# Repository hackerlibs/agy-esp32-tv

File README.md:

# AGY TV -- 把 Antigravity (AGY) 会话详情与进度显示在小电视上

把一块 ESP32-C3「小电视」（240x240 SPI 彩屏）改造成 **Antigravity (AGY)** 桌面状态显示器：屏幕实时显示当前 AGY 会话的状态（思考中 / 运行工具 / 等待输入 / 错误 / 完成 / 待机）、`update_steps` 步骤进度条与百分比、当前步骤说明、当前工具与命令/文件详情、模型名称、上下文与输出 Token 用量、子代理 / 后台任务数、用时和时钟。

主机侧通过 **AGY 生命周期 hooks**（`hooks.json`）抓取实时事件，并结合 `transcript.jsonl` 增量解析补齐真实模型名、Token 统计、思考摘要和最终回复；即使未重启 AGY 加载 hooks，桥接进程也可自动追踪最新活跃的 `transcript.jsonl`。

```
AGY hooks (6 种事件) ──► host/agy_tv.py hook ──► bridge 常驻进程 (+ transcript.jsonl 解析)
   (安全透传、永不阻塞)       (AF_UNIX DGRAM)         (状态机 + 心跳 + 串口自动重连)
                                                            │
                                                            ▼ USB Serial/JTAG (ZTV1 协议)
                                                      ESP32-C3 固件 ──► 240x240 彩屏
```

离屏渲染的全部 26 个界面见 `tools/uitest/run.sh` 生成的拼图（含中文界面），默认输出到 `/tmp/agy-tv-ui/sheet.png`。

> **想从零 DIY 这台设备 / 学习用万用表、示波器、USB-TTL、逻辑分析仪调试 ESP32 彩屏？**
> 详见 **[docs/ 硬件与调试文档中心](./docs/README.md)**（含 ESP32-C3 原理、屏幕选型与背光电路、四类仪器实战排障与 6 步点亮路线）。

## 显示内容一览

- **顶部状态栏**：`AGY TV` / `IDLE` / `THINKING` / `RUNNING` / `WAIT INPUT`（如 `ask_question`）/ `ERROR` / `DONE` / `NO HOST` / `NO USB` + 右上角链路状态 LED。
- **核心详情区**：
  - 思考中显示当前 Prompt 与调用轮次（`INV`）；
  - 运行工具显示工具名（`run_command` / `edit_file` / `subagent` / `grep` / `ask_question` 等）和命令/路径/参数摘要，超长文本自动水平往返滚动；
- **进度与活动区**：
  - 当 AGY 调用 `update_steps` 时，显示 `STEPS` 进度条、`完成/总数 百分比%` 与当前 `in_progress` 步骤标题；
  - 无步骤清单时自动切换为 `ACTIVITY`（当前目标/思考摘要）或 `PROGRESS` 动态活动条 + `STEP` 步数；
- **AGY 遥测条**：左侧显示解析出的实际模型名（如 `gemini-4-neon-high`），右侧显示上下文 Token（`CTX 89.4K`）；
- **底部统计与页脚**：左侧大字本轮用时（`ELAPSED`），右侧显示工具调用数（`TOOLS`）、子代理/后台任务数（`SUB` / `BG`）或输出 Token（`OUT`）、失败次数（`FAIL`）；页脚显示时钟与当前项目名（支持中文）。

## 硬件结论（来自对原厂固件的逆向）

原固件是 Arduino + TFT_eSPI 的「小电视」固件（开源项目 SmallDesktopDisplay 的定制版，源码见卖家提供的 `时钟/C3版本`）。屏幕引脚最初通过反汇编其 flash 备份得出，后与源码逐项核对一致：

| 项目 | 值 | 来源 |
|---|---|---|
| 主控 | ESP32-C3 (QFN32) rev 0.4，4MB flash | esptool flash-id |
| 屏幕 | 240x240、RGB565、IPS（需 INVON）、原生方向（MADCTL=0） | 原固件初始化命令表（rodata 0x3C28EE80） |
| SPI | mode 3，引脚 SCLK=3、MOSI=5（均为 FSPI 原生脚） | `SPIClass::begin(3, 5, 5, -1)` 反汇编 |
| DC / RST | GPIO2 / GPIO6（复位脉冲 20ms 低 + 150ms） | `pinMode`/`digitalWrite` 调用点反汇编 |
| CS | 未接（拉低） | `spi.begin(..., ss=-1)` |
| **背光** | **GPIO1，PWM 调光（LEDC）** | 源码 `User_Setup.h: #define TFT_BL 1`、`.ino: #define LCD_BL_PIN 1` + `analogWrite()` |

flash 分区（原厂）：nvs @0x9000、otadata、app0 @0x10000 (3MB)、spiffs @0x310000（相册）、coredump。
本固件只写 0x0..0x4B000（bootloader/分区表/app），**不碰 NVS 和相册**，随时可完整还原。

> **踩坑记录：背光**。排查黑屏先确认背光（`ZTV1 C bl`），再查显示数据。

## 仓库结构

```
main/            固件 (ESP-IDF v5.5, C)
  main.c           入口：面板初始化 → 链接 → 渲染任务
  panel.c          SPI 面板驱动（含 32KB DMA 分块）
  gfx.c            帧缓冲绘图层：脏行跟踪、混合文本（ASCII 5x8 + 中文 12px，无损 CJK 换行）
  zmodel.c         共享状态模型（含 AGY 模型/Token/步骤/子任务字段；演示模式样本）
  ui.c             AGY TV 九种状态界面；部件级局部重绘
  zlink.c          串口帧协议解析（向后兼容 ZTV1，容错忽略未知键与畸形行）
  port_esp.c       平台接缝（时钟/USB/互斥），使 ui/gfx/zmodel 可在桌面编译
  fonts/           生成的字库 + 三个开源字体的许可证
host/
  agy_tv.py        AGY bridge 常驻进程 + AGY hook 入口 + transcript.jsonl 追踪
  install_hooks.py 把 AGY hooks 写入 ~/.gemini/config/hooks.json（全局）或 .agents/hooks.json
  zcode_tv.py      兼容入口（转发到 agy_tv.py）
.agents/
  hooks.json       本仓库自带的便携工作区 AGY hooks 配置
tools/
  gen_fonts.py       字库生成（开发期，固件只 include 产物）
  uitest/            离屏渲染测试：无硬件验证全部界面 + 面板一致性校验（支持纯 Python 输出 PNG）
  build.sh           构建/烧录包装（支持 macOS /dev/cu.usbmodem* 与 Linux /dev/ttyACM*）
  flash_rfc2217.py   远程 RFC2217 专用刷机脚本（解决 ESP32-C3 USB 重枚举与 RFC2217 超时卡慢）
  monitor.sh         不会复位板子的串口监视器（支持本地串口与 rfc2217://）
  restore_original.sh 一键还原原厂固件（备份在 backup/，已校验）
backup/
  esp32c3_original_4MB.bin  原厂固件完整备份（含 WiFi 配置；勿提交，已在 .gitignore）
```

## 构建与烧录

依赖：ESP-IDF v5.5（如装在 `~/esp/esp-idf`，或通过 `IDF_PATH` 指定）。

```bash
tools/build.sh --flash        # 构建并烧录（自动找 /dev/cu.usbmodem* 或 /dev/ttyACM*）
tools/build.sh --monitor      # 烧录后打开串口监视（不会复位板子）
idf.py -p <port> menuconfig   # 引脚/时钟/旋转等全部可配 (AGY TV 菜单)
```

> **提示**：新版主机脚本 `host/agy_tv.py` 保持与旧版 v1 固件的 `ZTV1` 串口协议兼容；未重烧固件前也可直接显示状态、工具与步骤进度，重烧 v2.0.0 固件后即可解锁完整 AGY TV 界面（模型名、Token、步骤百分比、`SUB`/`BG` 计数等）。

无主机验证：烧录后屏幕自行显示 BOOT → NO HOST；也可以发 `ZTV1 C demo=1` 循环播放 AGY 演示数据（menuconfig 里 `ZTV_UI_DEMO_ON_BOOT` 可设为开机即演示）。

## 主机侧安装与启动

```bash
# 1. 安装 AGY 全局 hooks（~/.gemini/config/hooks.json，所有项目自动生效）
python3 host/install_hooks.py

# 或仅安装在某个工作区的 .agents/hooks.json：
# python3 host/install_hooks.py --workspace

# 2. 启动串口桥接（本地 USB 自动发现，也支持 rfc2217://；无需设备时可加 --dry-run 预览帧）
python3 host/agy_tv.py bridge --daemon
# 远程 RFC2217 桥接示例（也可通过环境变量 AGY_TV_PORT 指定）：
# python3 host/agy_tv.py bridge --port 'rfc2217://127.0.0.1:4000?ign_set_control' --daemon

# 3. 查看桥接状态、日志，或在线调节背光亮度（无需停止桥接）
python3 host/agy_tv.py status
tail -f /tmp/agy-tv.log
python3 host/agy_tv.py bl 80         # 设置背光亮度 0..100%（实时生效）
python3 host/agy_tv.py bl            # 查询当前亮度、原始 PWM 占空比与极性
python3 host/agy_tv.py bl --raw 50   # 直接设置 8-bit LEDC 原始占空比 (0..256)
python3 host/agy_tv.py bl --inv 1    # 切换背光极性（1=低电平亮/默认，0=高电平亮）
```

- Hooks 严格遵循 AGY `hooks.json` 契约：`PreToolUse` 返回 `{"decision": "allow"}`（交给默认权限策略，**绝不**绕过授权确认），`Stop` 返回 `{"decision": "stop"}`，其余返回 `{}`，永远 exit 0，桥接未开或板子未插都不会阻塞 AGY。
- 卸载 hooks：`python3 host/install_hooks.py --remove`（或加 `--workspace`）。
- 即使尚未重启 AGY 会话，bridge 也会自动扫描 `~/.gemini/{antigravity-cli,antigravity,antigravity-ide}/brain/*/.system_generated/logs/transcript.jsonl` 追踪最近活跃会话（可用 `--no-watch` 关闭）。

## 远程刷机与远程驱动教程（RFC2217 + SSH 反向代理）

如果你的 **AGY 运行在远程 Linux 服务器**，而 **ESP32-C3 插在本地 Mac/电脑上**，可以通过 `esp_rfc2217_server` + SSH 反向端口转发，在远程服务器上直接编译、刷机并实时驱动小电视。

### 第 1 步：在本地电脑（插着 ESP32 的机器）启动 RFC2217 服务端

> **关键踩坑（ESP32-C3 内置 USB-Serial/JTAG 必看）**：
> `esp_rfc2217_server.py` 默认会拦截客户端的 DTR/RTS 并在服务端执行 `UnixTightReset`（传统 CP2102/CH340 串口芯片用的时序），会导致 ESP32-C3 每次复位都进入 `boot:0xd (SPI_FAST_FLASH_BOOT)` 而无法进入下载模式。
> **解法**：写入 `esptool.cfg` 指定 ESP32-C3 USB-Serial/JTAG 的下载模式复位时序，并通过 `ESPTOOL_CFGFILE` 加载：

```bash
# 1. 创建 ESP32-C3 USB-Serial/JTAG 复位配置
cat > /tmp/esptool_c3.cfg <<'EOF'
[esptool]
custom_reset_sequence = R0|D0|W0.1|D1|R0|W0.1|R1|D0|R1|W0.1|D0|R0
EOF

# 2. 启动 RFC2217 服务端（启动输出必须看到 Loaded custom configuration from /tmp/esptool_c3.cfg）
ESPTOOL_CFGFILE=/tmp/esptool_c3.cfg \
  ~/.espressif/python_env/idf5.5_py3.13_env/bin/esp_rfc2217_server.py \
  -v -p 4000 /dev/cu.usbmodem14201
```

### 第 2 步：把本地 4000 端口反向代理到远程 Linux 服务器

在本地再开一个终端（或合并进你的 SSH 登录命令）：

```bash
ssh -N -R 4000:127.0.0.1:4000 <user>@<remote-server>
```

在远程服务器上可用 `ss -tlnp | grep 4000` 确认 `127.0.0.1:4000` 已监听。

### 第 3 步：在远程服务器编译并远程刷机

```bash
# 0. 如果 bridge 正在运行，先停掉（esp_rfc2217_server 同一时间只接受一个 TCP 连接）
kill $(cat /tmp/agy-tv.bridge.pid) 2>/dev/null || true

# 1. 编译固件（仅需安装 esp32c3 目标的 ESP-IDF v5.5）
tools/build.sh

# 2. 使用远程刷机脚本写入（分段写入 0x0 / 0x8000 / 0x10000，不碰 NVS 和原厂相册）
python3 tools/flash_rfc2217.py

# 之后如果只改了应用代码（没改分区表/bootloader），可只刷主程序更快：
python3 tools/flash_rfc2217.py --app-only
```

> **为什么要用 `tools/flash_rfc2217.py` 而不是裸跑 `esptool.py`？**（实测踩坑总结）
> 1. **参数拼写**：pyserial RFC2217 的选项是单数 `ign_set_control`（不是 `ign_set_controls`）。
> 2. **打开端口的复位竞态**：`esp_rfc2217_server` 在 TCP 连上（`DTR_ON`）时就会触发 `custom_reset_sequence`（耗时约 0.3s）；若客户端再跑 `default_reset`，发出的 `DTR_OFF`/`RTS_OFF` 会把芯片踢出下载模式。脚本使用 `--before no_reset`，连上后等待 0.6s 再发 `SYNC`（并将 `SYNC_TIMEOUT` 调到 0.5s 适应隧道 RTT）。
> 3. **macOS USB 重枚举（`Errno 6: Device not configured`）**：在 ESP32-C3 USB-Serial/JTAG 上上传并切换 RAM stub 时容易触发 macOS 重新枚举 `/dev/cu.usbmodem*`，导致服务端 fd 失效。脚本使用 `--no-stub --compress` 留在芯片 mask ROM 中直接解压写入，稳定不掉线。
> 4. **pyserial RFC2217 卡慢 10 倍**：`esptool` 每写入一个块都会保存/恢复 `port.timeout`，而 pyserial 的 `rfc2217.Serial.timeout` 每次被赋值都会重新发起 4 项 Telnet 串口参数协商（把刷机拖慢到 ~4 kbit/s）。脚本在 `open()` 之后覆写 `timeout` setter 跳过无意义的远端协商，实测提速约 9 倍（459KB 压缩为 224KB，约 105 秒刷完，有效速率 ~35 kbit/s）。

### 第 4 步：在远程服务器启动 AGY 实时桥接

刷完固件后，直接把 `agy_tv.py` 连到反向代理端口，即可让本地桌面的小电视实时显示远程服务器上的 AGY 详情进度：

```bash
# 安装远程服务器全局 AGY hooks（~/.gemini/config/hooks.json）
python3 host/install_hooks.py

# 启动远程 RFC2217 桥接（会自动跳过 rfc2217 不支持的 write_timeout，并在连上后退出下载模式正常启动固件）
nohup python3 host/agy_tv.py bridge \
  --port 'rfc2217://127.0.0.1:4000?ign_set_control' \
  --daemon >/dev/null 2>&1 </dev/null

# 验证连接与实时日志
python3 host/agy_tv.py status
tail -f /tmp/agy-tv.log
```

## 真机实测性能（AGY TV v2.0.0）

| 项目 | 实测值 |
|---|---|
| 固件体积 | `449 KB`（`0x70400`，3MB app 分区空闲 85%） |
| 空闲堆内存 | `187.9 KB` |
| 静止帧渲染耗时 | `28 us`（0 行 SPI 流量） |
| 动画帧渲染耗时 | `~10.3 ms` |
| 最慢全屏刷新 | `41.0 ms`（20fps 预算 50ms） |
| 背光状态 | GPIO1 PWM `duty=255` |

恢复原厂固件（天气时钟 + 相册，含全部设置）：

```bash
tools/restore_original.sh
```

## 串口协议（115200，行式 ASCII，兼容 ZTV1）

主机 → 设备（每帧是完整快照，未知键自动忽略）：

```
ZTV1 S st=<idle|think|tool|perm|err|done> tool="run_command" n=7 f=1 el=42 todo=2/4
      cur="当前步骤" msg="命令或提示文本" proj="esp32_tv" sid="a3653af3"
      clk="14:02:11" date="2026-11-27 FRI"
      model="gemini-4-neon-high" inv=4 step=18 ctx=89400 out=3720 sub=1 bg=1
ZTV1 C ping | stats | get | bl[=<0..100>] | bl_raw=<0..256> | bl_inv=<0|1> | demo=<0|1> | rot=<0..3> | reboot
```

设备 → 主机：`ZTV1 R hello|pong|state ...|stats ...|bl ...`。`msg/cur/proj` 为 UTF-8，设备用 GB2312 字库渲染（7445 字，~190KB 在 flash，不占 RAM）；字库外的字符（emoji 等）跳过。

## 疑难排解

- **屏幕全黑但串口正常（`ZTV1 C stats` 帧数在涨）**：检查背光 `ZTV1 C bl`。
- **板子看起来「死」了 / 启动不起来**：ESP32-C3 的 USB-Serial/JTAG 用 DTR/RTS 控制 EN/IO0。不要用会拉低 IO0 的普通串口工具；重新插拔 USB 或使用 `tools/monitor.sh` 即可。
- **端口被占用**：桥接运行时独占端口。先 `kill $(cat /tmp/agy-tv.bridge.pid)`。
- **屏幕方向不对**：`python3 host/agy_tv.py send "ZTV1 C rot=0"`（支持 `0..3`）。

## 测试

- `tools/uitest/run.sh`：在桌面用 `clang` 或 `gcc`（开启 `-Wall -Wextra -Werror` + ASan/UBSan）编译真实的 `ui.c`/`gfx.c`/`zmodel.c`，渲染 26 个 AGY 屏幕场景，并逐帧校验模拟面板与帧缓冲逐字节一致（598 帧 0 差异）。无需 Pillow 也能通过纯 Python 生成 `sheet.png` 与单张 PNG。

## 字体许可

`main/fonts/` 内含三份许可证：Press Start 2P（OFL-1.1）、Spleen（BSD-2-Clause）、Cubic 11（OFL-1.1，基于 M+ BITMAP FONTS）。均允许固件捆绑；生成器 `tools/gen_fonts.py`。

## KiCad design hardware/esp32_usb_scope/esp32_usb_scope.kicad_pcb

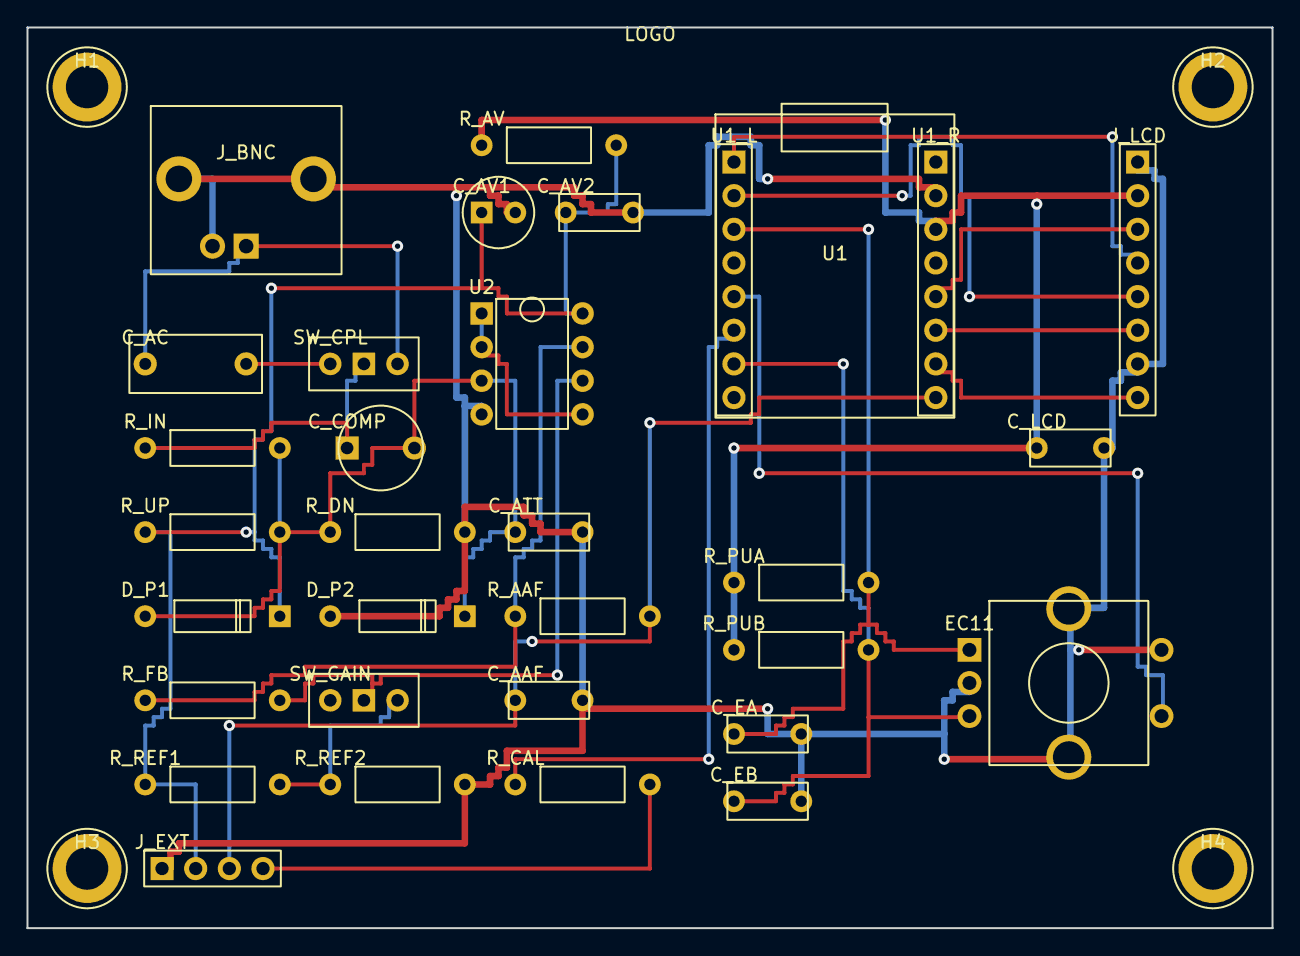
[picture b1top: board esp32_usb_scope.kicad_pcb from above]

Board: 2 copper layers, 94.0 x 68.0 mm, 37 parts (0 on the bottom side), 22 nets.

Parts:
C_AAF: 1nF; C_Disc_D5.0mm_P5.08mm
C_AC: 0.1u 250V; C_Film_L10mm_P7.62mm
C_ATT: 180pF; C_Disc_D5.0mm_P5.08mm
C_AV1: 10uF; CP_Radial_D5.0mm_P2.54mm
C_AV2: 100n; C_Disc_D5.0mm_P5.08mm
C_COMP: 5-30pF; C_Trim_6mm_P5.08mm
C_EA: 10nF; C_Disc_D5.0mm_P5.08mm
C_EB: 10nF; C_Disc_D5.0mm_P5.08mm
C_LCD: 100nF; C_Disc_D5.0mm_P5.08mm
D_P1, D_P2: 1N4148; D_DO-35_P10.16mm
EC11: TIME/TRIG; RotaryEncoder_Alps_EC11E-Switch_Vertical_H20mm
H1, H2, H3, H4: M3; MountingHole_3.2mm_M3
J_BNC: BNC-JACK; Connector_BNC_RA_P10.16mm
J_EXT: AFE-OUT-4P; PinHeader_1x04_P2.54mm
J_LCD: ST7789-8P; PinHeader_1x08_P2.54mm
LOGO: ESP32-USB-SCOPE; Silkscreen
R_AAF: 1k; R_Axial_DIN0207_L6.3mm_P10.16mm
R_AV: 10R; R_Axial_DIN0207_L6.3mm_P10.16mm
R_CAL: 1k; R_Axial_DIN0207_L6.3mm_P10.16mm
R_DN: 100k; R_Axial_DIN0207_L6.3mm_P10.16mm
R_FB: 39k; R_Axial_DIN0207_L6.3mm_P10.16mm
R_IN: 910k; R_Axial_DIN0207_L6.3mm_P10.16mm
R_PUA: 10k; R_Axial_DIN0207_L6.3mm_P10.16mm
R_PUB: 10k; R_Axial_DIN0207_L6.3mm_P10.16mm
R_REF1: 22k; R_Axial_DIN0207_L6.3mm_P10.16mm
R_REF2: 20k; R_Axial_DIN0207_L6.3mm_P10.16mm
R_UP: 100k; R_Axial_DIN0207_L6.3mm_P10.16mm
SW_CPL: AC/DC; SW_Slide_SPDT_P2.54mm
SW_GAIN: X1/X5; SW_Slide_SPDT_P2.54mm
U1: ESP32-C3 SuperMini; Module_ESP32-C3_SuperMini
U1_L: ESP32-C3-SM-L; PinHeader_1x08_P2.54mm
U1_R: ESP32-C3-SM-R; PinHeader_1x08_P2.54mm
U2: MCP6002; DIP-8_W7.62mm_Socket

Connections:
3V3: C_LCD.1, J_LCD.2, R_AV.1, R_PUA.1, R_PUB.1, U1_R.3
AFE_N1: C_ATT.1, C_COMP.2, D_P1.1, D_P2.2, R_DN.1, R_IN.2, R_UP.2, U2.3
AFE_OUT: C_AAF.1, J_EXT.3, R_AAF.2, U1_R.8
AMP_OUT: R_AAF.1, R_FB.1, U2.7
AVDD: C_AV1.1, C_AV2.1, D_P1.2, J_EXT.2, R_AV.2, R_REF1.1, R_UP.1, U2.8
BNC_AC: C_AC.2, SW_CPL.1
BNC_IN: C_AC.1, J_BNC.SIG, SW_CPL.3
CAL_1KHZ: J_EXT.4, R_CAL.2
CAL_PWM: R_CAL.1, U1_L.6
CPL_OUT: C_COMP.1, R_IN.1, SW_CPL.2
EC11_A: C_EA.1, EC11.A, R_PUA.2, U1_L.3
EC11_B: C_EB.1, EC11.B, R_PUB.2, U1_L.7
EC11_SW: EC11.S1, U1_L.5
GND: C_AAF.2, C_ATT.2, C_AV1.2, C_AV2.2, C_EA.2, C_EB.2, C_LCD.2, D_P2.1, EC11.C, EC11.MP1, EC11.MP2, EC11.S2, J_BNC.GND, J_BNC.SH1, J_BNC.SH2, J_EXT.1, J_LCD.1, J_LCD.7, R_DN.2, R_REF2.2, U1_R.2, U2.4
G_INV: R_FB.2, SW_GAIN.2, U2.6
LCD_BL: J_LCD.8, U1_R.7
LCD_DC: J_LCD.6, U1_R.6
LCD_MOSI: J_LCD.4, U1_L.1
LCD_RST: J_LCD.5, U1_L.2
LCD_SCLK: J_LCD.3, U1_R.5
VREF_DIV: R_REF1.2, R_REF2.1, SW_GAIN.3
V_BUF: U2.1, U2.2, U2.5

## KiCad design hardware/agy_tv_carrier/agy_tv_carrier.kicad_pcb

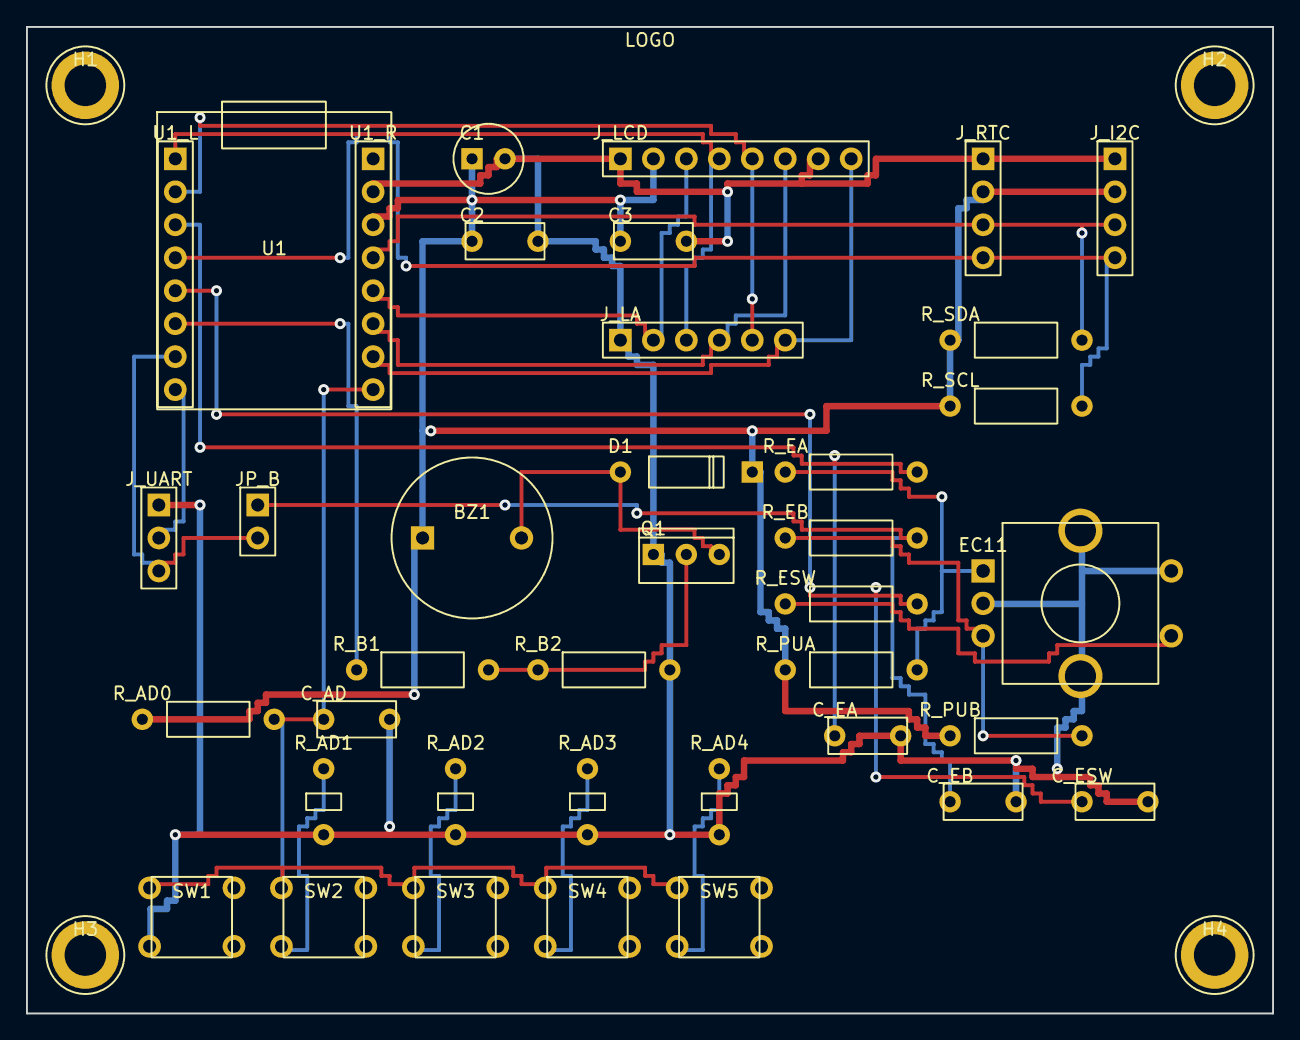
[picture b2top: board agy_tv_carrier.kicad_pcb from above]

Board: 2 copper layers, 96.0 x 76.0 mm, 44 parts (0 on the bottom side), 25 nets.

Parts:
BZ1: 12mm-PASSIVE; Buzzer_12x9.5mm_P7.62mm
C1: 10uF; CP_Radial_D5.0mm_P2.54mm
C2, C3: 0.1uF; C_Disc_D5.0mm_P5.08mm
C_AD: 100nF; C_Disc_D5.0mm_P5.08mm
C_EA: 10nF; C_Disc_D5.0mm_P5.08mm
C_EB: 10nF; C_Disc_D5.0mm_P5.08mm
C_ESW: 100nF; C_Disc_D5.0mm_P5.08mm
D1: 1N4148; D_DO-35_P10.16mm
EC11: EC11E-SW; RotaryEncoder_Alps_EC11E-Switch_Vertical_H20mm
H1, H2, H3, H4: M3; MountingHole_3.2mm_M3
JP_B: EC11B-JMP; PinHeader_1x02_P2.54mm
J_I2C: I2C-EXP-4P; PinHeader_1x04_P2.54mm
J_LA: SCOPE-LA-6P; PinHeader_1x06_P2.54mm
J_LCD: ST7789-8P; PinHeader_1x08_P2.54mm
J_RTC: DS3231-4P; PinHeader_1x04_P2.54mm
J_UART: USB-TTL-3P; PinHeader_1x03_P2.54mm
LOGO: AGY-TV-CARRIER; Silkscreen
Q1: S8050; TO-92_Inline_Wide_P2.54mm
R_AD0: 10k; R_Axial_DIN0207_L6.3mm_P10.16mm
R_AD1: 2.2k 1%; R_Axial_DIN0207_L6.3mm_P10.16mm
R_AD2: 5.6k 1%; R_Axial_DIN0207_L6.3mm_P10.16mm
R_AD3: 12k 1%; R_Axial_DIN0207_L6.3mm_P10.16mm
R_AD4: 33k 1%; R_Axial_DIN0207_L6.3mm_P10.16mm
R_B1: 1k; R_Axial_DIN0207_L6.3mm_P10.16mm
R_B2: 10k; R_Axial_DIN0207_L6.3mm_P10.16mm
R_EA: 1k; R_Axial_DIN0207_L6.3mm_P10.16mm
R_EB: 1k; R_Axial_DIN0207_L6.3mm_P10.16mm
R_ESW: 1k; R_Axial_DIN0207_L6.3mm_P10.16mm
R_PUA: 10k; R_Axial_DIN0207_L6.3mm_P10.16mm
R_PUB: 10k; R_Axial_DIN0207_L6.3mm_P10.16mm
R_SCL: 4.7k; R_Axial_DIN0207_L6.3mm_P10.16mm
R_SDA: 4.7k; R_Axial_DIN0207_L6.3mm_P10.16mm
SW1: BACK; SW_PUSH_6mm_H4.3mm
SW2: UP; SW_PUSH_6mm_H4.3mm
SW3: OK; SW_PUSH_6mm_H4.3mm
SW4: DOWN; SW_PUSH_6mm_H4.3mm
SW5: MUTE; SW_PUSH_6mm_H4.3mm
U1: ESP32-C3 SuperMini; Module_ESP32-C3_SuperMini
U1_L: ESP32-C3-SM-L; PinHeader_1x08_P2.54mm
U1_R: ESP32-C3-SM-R; PinHeader_1x08_P2.54mm

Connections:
3V3: BZ1.1, C1.1, C2.1, C3.1, D1.2, J_I2C.2, J_LCD.2, J_RTC.2, R_AD0.1, R_PUA.1, R_PUB.1, R_SCL.1, R_SDA.1, U1_R.3
ADC_KEY: C_AD.1, R_AD0.2, SW1.1, SW2.1, SW3.1, SW4.1, SW5.1, U1_R.8
AD_K2: R_AD1.1, SW2.3
AD_K3: R_AD2.1, SW3.3
AD_K4: R_AD3.1, SW4.3
AD_K5: R_AD4.1, SW5.3
BUZ_B: Q1.2, R_B1.2, R_B2.1
BUZ_C: BZ1.2, D1.1, Q1.3
BUZ_PWM: R_B1.1, U1_L.6
EC11_A: C_EA.1, R_EA.2, U1_L.3
EC11_A_RAW: EC11.A, R_EA.1, R_PUA.2
EC11_B_RAW: EC11.B, R_EB.1, R_PUB.2
EC11_B_SIG: C_EB.1, JP_B.1, R_EB.2
EC11_SW: C_ESW.1, R_ESW.2, U1_L.5
EC11_SW_RAW: EC11.S1, R_ESW.1
GND: C1.2, C2.2, C3.2, C_AD.2, C_EA.2, C_EB.2, C_ESW.2, EC11.C, EC11.MP1, EC11.MP2, EC11.S2, J_I2C.1, J_LA.1, J_LCD.1, J_LCD.7, J_RTC.1, J_UART.1, Q1.1, R_AD1.2, R_AD2.2, R_AD3.2, R_AD4.2, R_B2.2, SW1.3, U1_R.2
I2C_SCL: J_I2C.4, J_RTC.4, R_SCL.2, U1_L.4
I2C_SDA: J_I2C.3, J_RTC.3, R_SDA.2, U1_R.4
LCD_BL: J_LA.6, J_LCD.8, U1_R.7
LCD_DC: J_LA.4, J_LCD.6, U1_R.6
LCD_MOSI: J_LA.3, J_LCD.4, U1_L.1
LCD_RST: J_LA.5, J_LCD.5, U1_L.2
LCD_SCLK: J_LA.2, J_LCD.3, U1_R.5
UART_RX: JP_B.2, J_UART.3, U1_L.7
UART_TX: J_UART.2, U1_L.8

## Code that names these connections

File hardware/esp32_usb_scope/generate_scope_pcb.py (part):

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       - U2A: High-Z unity-gain buffer
       - U2B: Switchable x1 (+-20V) / x4.7 (+-4V) gain stage around 1.57V virtual mid-rail
  6. Anti-aliasing RC filter (R_AAF 1k + C_AAF 1nF) + Schottky ADC clamp
  7. 1kHz Probe-Compensation Calibration Hook (CAL_1KHZ from GPIO10 via 1k)
  8. Analog power RC filter (R_AV 10R + C_AV1 10uF + C_AV2 0.1uF -> AVDD_3V3)

Digital / Display / Expansion:
  - U1: ESP32-C3 SuperMini (2x8P 2.54mm, USB-C TOP)
  - J_LCD: 1.54" 8-pin ST7789 IPS LCD header (standalone display)
  - EC11: Rotary encoder w/ push switch (timebase / trigger / run-stop)
  - J_EXT: 4-pin AFE breakout (GND, AVDD, AFE_OUT, CAL_1KHZ) to connect directly
           to ESP32-S3 + AD9280 or ESP32-P4 + MIPI smartphone screen!

Board size: 94.0 x 68.0 mm (<= 100x100mm JLCPCB free 2-layer coupon eligible).
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                   lcsc="C2128", desc="1N4148 Under-voltage Clamp to GND (0V)")

    # 5. Dual Rail-to-Rail Op-Amp U2 (DIP-8: MCP6002 / TLC2272 / OPA2350)
    # Pin1=OUTA(V_BUF), Pin2=INA-(V_BUF), Pin3=INA+(AFE_N1), Pin4=VSS(GND)
    # Pin5=INB+(V_BUF), Pin6=INB-(G_INV), Pin7=OUTB(AMP_OUT), Pin8=VDD(AVDD)
    add_dip8_ic(comps, "U2", "MCP6002", 34.29, 21.59,
                ["V_BUF", "V_BUF", "AFE_N1", "GND", "V_BUF", "G_INV", "AMP_OUT", "AVDD"])

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    base.add_resistor(comps, "R_FB", "39k", 8.89, 50.80, "AMP_OUT", "G_INV", horiz=True,
                      lcsc="C61274", desc="39k 1% 1/4W U2B Feedback Resistor (x4.7 gain)")
    add_slide_switch_spdt(comps, "SW_GAIN", "X1/X5", 22.86, 50.80, "G_INV", "GAIN_SW", "VREF_DIV",
                          desc="Gain Switch: Open/1-2=x1 (+-20V), 2-3=x4.7 (+-4V) — tie pin 1 & 2 to G_INV via short")
    # Wait: SPDT connects pin 2 (COM) to pin 1 or pin 3!
    # So put net1="NC_G" (unused), net_com="G_INV", net3="VREF_DIV" -> left = x1 (open), right = x4.7 (closed)!
    comps[-1].pads[0].net = ""
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
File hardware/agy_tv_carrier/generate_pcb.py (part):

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  - 5-key ADC resistor-ladder keypad on GPIO0 (ADC1_CH0)
  - Passive electromagnetic buzzer driver (S8050 NPN + 1N4148 flyback diode)
  - DS3231 RTC header + parallel I2C expansion header (GPIO4=SDA, GPIO8=SCL)
  - USB-TTL debug header (GPIO20/21) + EC11_B isolate jumper + 6-pin Scope/LA header

Outputs in hardware/agy_tv_carrier/:
  - gerber/* and agy_tv_carrier_jlcpcb_gerber.zip  (RS-274X + Excellon drill)
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    add_cap_ceramic(comps, "C3", "0.1uF", 45.72, 16.51, "3V3", "GND", horiz=True, lcsc="C192578", desc="0.1uF 50V Ceramic (LCD VCC Decoupling)")

    # 3. DS3231 RTC + I2C Expansion Headers (top-right)
    i2c_pins = [("GND", "GND"), ("3V3", "3V3"), ("SDA", "I2C_SDA"), ("SCL", "I2C_SCL")]
    add_header(comps, "J_RTC", "DS3231-4P", 73.66, 10.16, i2c_pins, horiz=False,
               lcsc="C2883690", desc="1x4P 2.54mm Female Header (DS3231 RTC Module)", label_side="left")
    add_header(comps, "J_I2C", "I2C-EXP-4P", 83.82, 10.16, i2c_pins, horiz=False,
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               lcsc="C2337", desc="1x6P 2.54mm Male Header (Oscilloscope / Logic Analyzer Test Points)", label_side="bottom")

    # 5. USB-TTL Debug Header + EC11_B Jumper (middle-left)
    uart_pins = [("GND", "GND"), ("TX", "UART_TX"), ("RX", "UART_RX")]
    add_header(comps, "J_UART", "USB-TTL-3P", 10.16, 36.83, uart_pins, horiz=False,
               lcsc="C2337", desc="1x3P 2.54mm Male Header (USB-TTL 3.3V Debug)", label_side="left")
    jp_pins = [("B", "EC11_B_SIG"), ("RX", "UART_RX")]
    add_header(comps, "JP_B", "EC11B-JMP", 17.78, 36.83, jp_pins, horiz=False,
               lcsc="C2337", desc="1x2P 2.54mm Jumper (Short to connect EC11_B to GPIO20)", label_side="right")

    # 6. Passive Electromagnetic Buzzer Driver (middle-center-left)
    add_buzzer_12mm(comps, "BZ1", "12mm-PASSIVE", 34.29, 39.37, "3V3", "BUZ_C",
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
